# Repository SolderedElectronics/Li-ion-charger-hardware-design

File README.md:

# Li-ion charger Hardware design

## About the product

|  |
| :----------------------------------------------------------: |
|      [Buy Li-ion charger](https://www.solde.red/333013)      |

Lithium batteries can’t be charged as regular batteries or devices. Instead, you’ll need a li-ion charger such as this one. Integrated with the CC/CV charging technology, it is the simplest way to charge a lithium-ion battery.

The board has a USB Type-C connector for power, a JST-type connector for batteries, the charging circuit, and two status LEDs.

## Repository contents

All Soldered Electronics hardware designed in KiCAD, and repositories are organized in the following way:

- CAD folder - contains KiCAD files (Schematics, Board, Panel Board), sorted by version. Change log lists all changes between versions.
- OUTPUTS - contains useful files, such as Bill of Materials (BOM), PDF of schematics, 3D .step file of the board and gerber files, sorted by version. 
- OUTPUTS -> Compliance - Certificates and useful legal stuff. 

## Want to contribute?

Please feel free to submit a pull request if you have any contributions. We encourage you to submit an issue or pull request if you find a bug. 

## About Soldered

At Soldered, we design and manufacture a wide selection of electronic products to help you turn your ideas into acts and bring you one step closer to your final project. Our products are intented for makers and crafted in-house by our experienced team in Osijek, Croatia. We believe that sharing is a crucial element for improvement and innovation, and we work hard to stay connected with all our makers regardless of their skill or experience level. Therefore, all our products are open-source. Finally, we always have your back. If you face any problem concerning either your shopping experience or your electronics project, our team will help you deal with it, offering efficient customer service and cost-free technical support anytime. Some of those might be useful for you:

- [Web Store](https://www.soldered.com/shop)
- [Tutorials & Projects](https://soldered.com/learn)
- [Community & Technical support](https://soldered.com/community)

## License info

All Soldered open-source hardware (OSH) is under The TAPR Open Hardware License. Read more in the LICENSE file. 

No warranty - all designs in this repository are distributed in the hope that they will be useful, but without any warranty. They are provided "AS IS", therefore without warranty of any kind, either expressed or implied. The entire quality and performance of what you do with the contents of this repository are your responsibility. In no event, Soldered Electronics will be liable for your damages, losses, including any general, special, incidental or consequential damage arising out of the use or inability to use the contents of this repository. 

## Have fun! 
And thank you from your fellow makers at Soldered Electronics.

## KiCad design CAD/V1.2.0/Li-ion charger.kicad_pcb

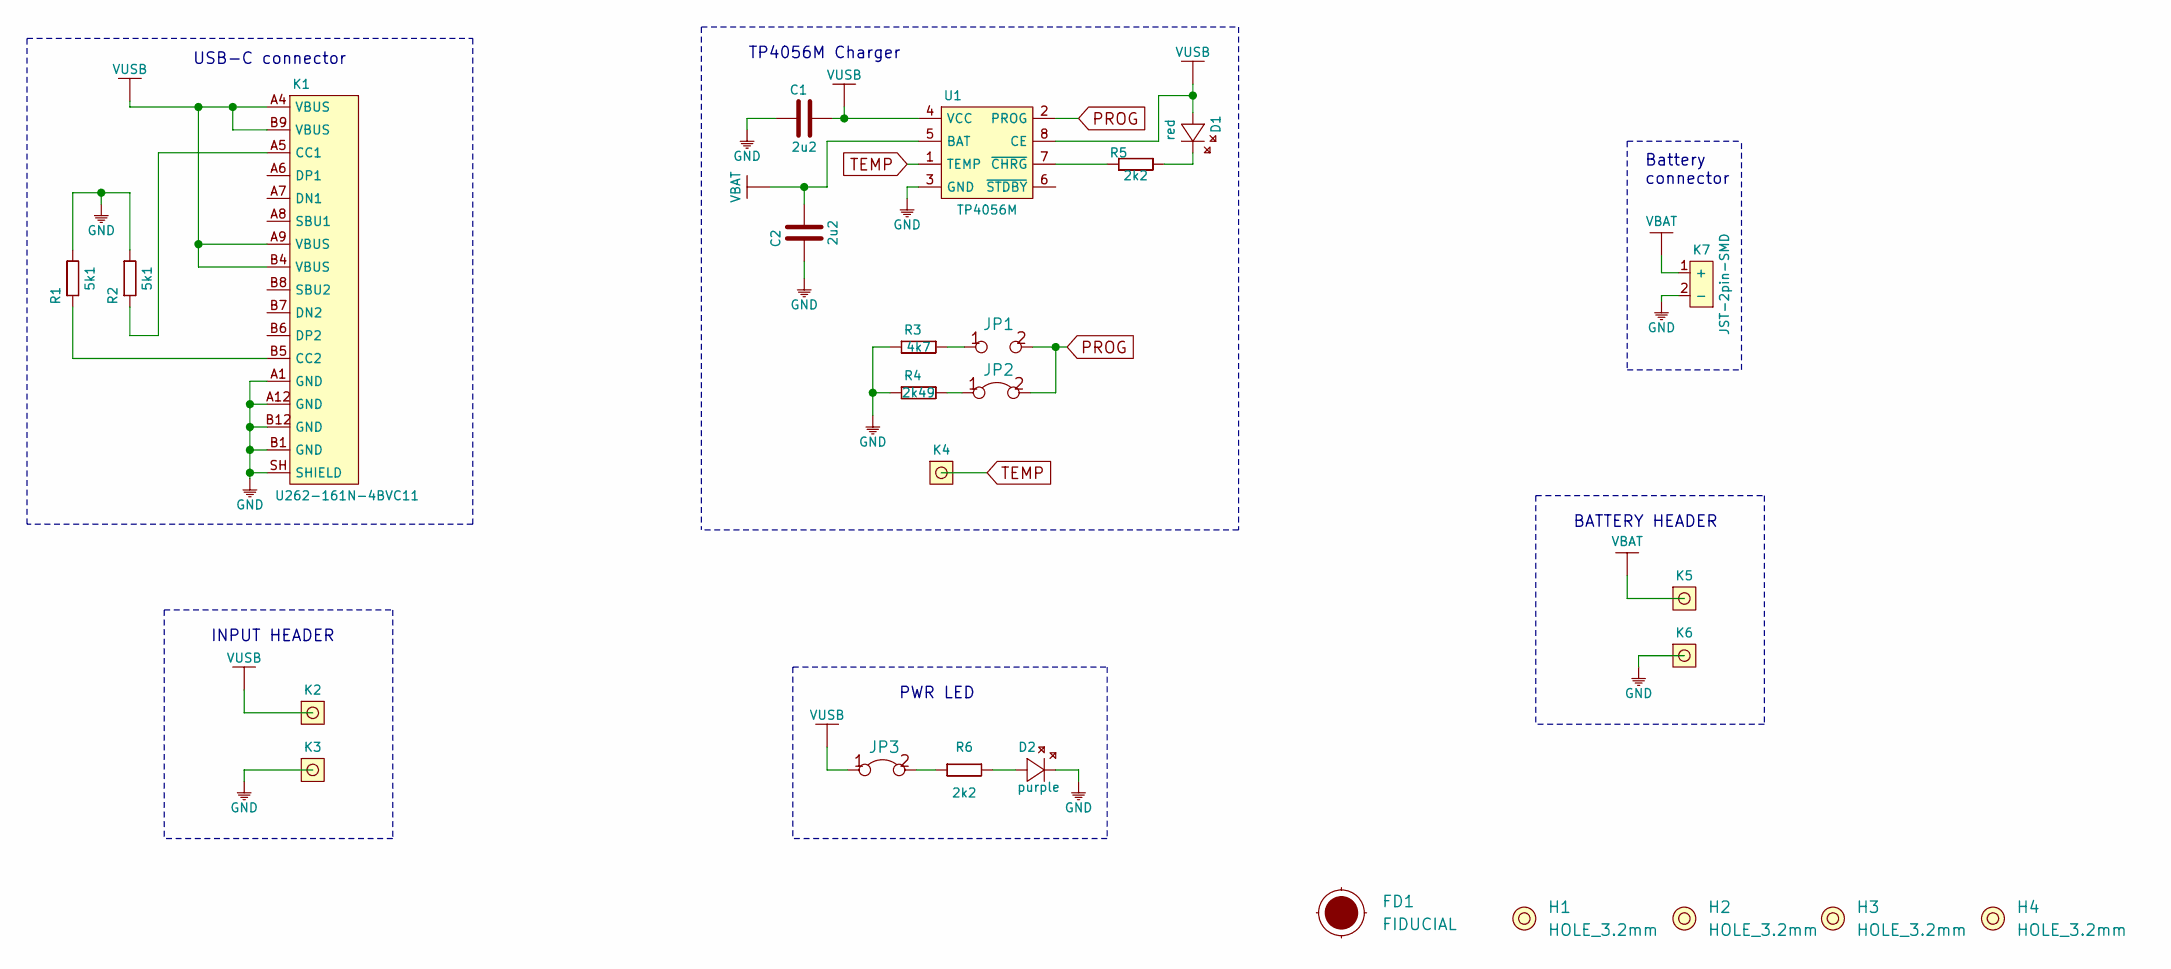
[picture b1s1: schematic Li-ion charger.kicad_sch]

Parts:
C1, C2: 2u2; 0603C
D1: red; 0402LED
D2: purple; 0402LED
FD1: FIDUCIAL; FIDUCIAL_23
H1, H2, H3, H4: HOLE_3.2mm
JP1: SMD_JUMPER
JP2: SMD-JUMPER-CONNECTED; SMD_JUMPER_CONNECTED
JP3: SMD-JUMPER-CONNECTED_TRACE_SLODERMASK
K1: U262-161N-4BVC11
K2, K3, K4, K5, K6: HEADER_MALE_1X1
K7: JST-2pin-SMD
R1, R2: 5k1; 0603R
R3: 4k7; 0603R
R4: 2k49; 0603R
R5, R6: 2k2; 0402R
U1: TP4056M; TP4056M-MSOP8

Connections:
GND: C1.1, C2.1, D2.2 (K), K1.A1 (GND), K1.A12 (GND), K1.B1 (GND), K1.B12 (GND), K1.SH (SHIELD), K3.1, K6.1, K7.2 (-), R1.2, R2.2, R3.1, R4.1, U1.3 (GND)
unnamed: D1.2 (K), R5.2
unnamed: D2.1 (A), R6.2
unnamed: JP1.1, R3.2
unnamed: JP2.1, R4.2
unnamed: JP3.2, R6.1
unnamed: K1.A5 (CC1), R2.1
unnamed: K1.B5 (CC2), R1.1
unnamed: R5.1, U1.7 (~CHRG)
PROG: JP1.2, JP2.2, U1.2 (PROG)
TEMP: K4.1, U1.1 (TEMP)
VBAT: C2.2, K5.1, K7.1 (+), U1.5 (BAT)
VUSB: C1.2, D1.1 (A), JP3.1, K1.A4 (VBUS), K1.A9 (VBUS), K1.B4 (VBUS), K1.B9 (VBUS), K2.1, U1.4 (VCC), U1.8 (CE)

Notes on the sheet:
INPUT HEADER
USB-C connector
TP4056M Charger
PWR LED
Battery connector
BATTERY HEADER

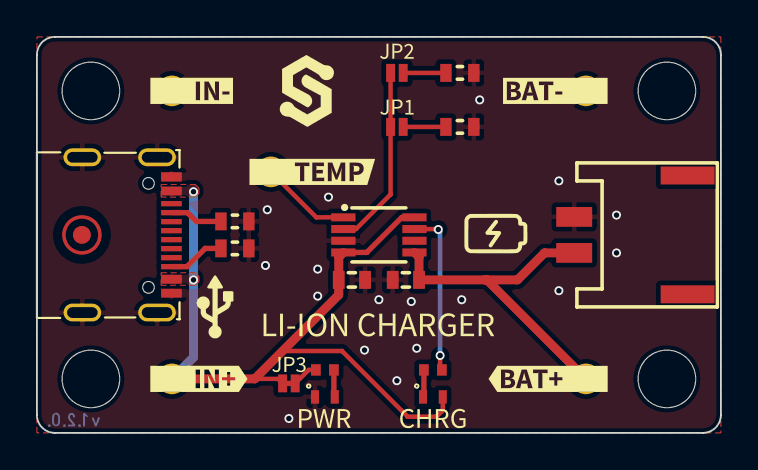
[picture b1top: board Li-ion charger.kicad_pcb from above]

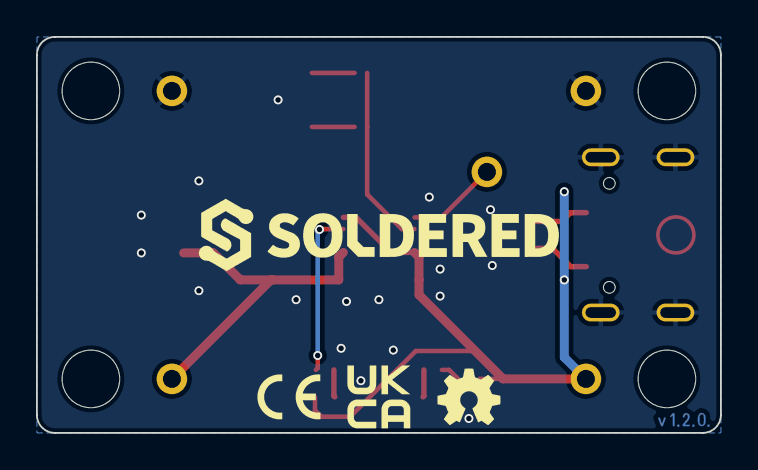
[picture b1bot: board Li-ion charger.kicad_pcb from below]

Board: 2 copper layers, 38.0 x 22.0 mm, 37 parts (4 on the bottom side), 13 nets.

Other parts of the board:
kibuzzard-669504AA: G***; kibuzzard-669504AA
kibuzzard-669504CA: G***; kibuzzard-669504CA
kibuzzard-669504E0: G***; kibuzzard-669504E0
kibuzzard-669504EC: G***; kibuzzard-669504EC
kibuzzard-6695049F: G***; kibuzzard-6695049F
kibuzzard-66950404: G***; kibuzzard-66950404
kibuzzard-66950472: G***; kibuzzard-66950472
kibuzzard-66950480: G***; kibuzzard-66950480
kibuzzard-66950503: G***; kibuzzard-66950503
kibuzzard-66950510: G***; kibuzzard-66950510
kibuzzard-66950525: G***; kibuzzard-66950525

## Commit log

2022-08-06 Updating open source files.
